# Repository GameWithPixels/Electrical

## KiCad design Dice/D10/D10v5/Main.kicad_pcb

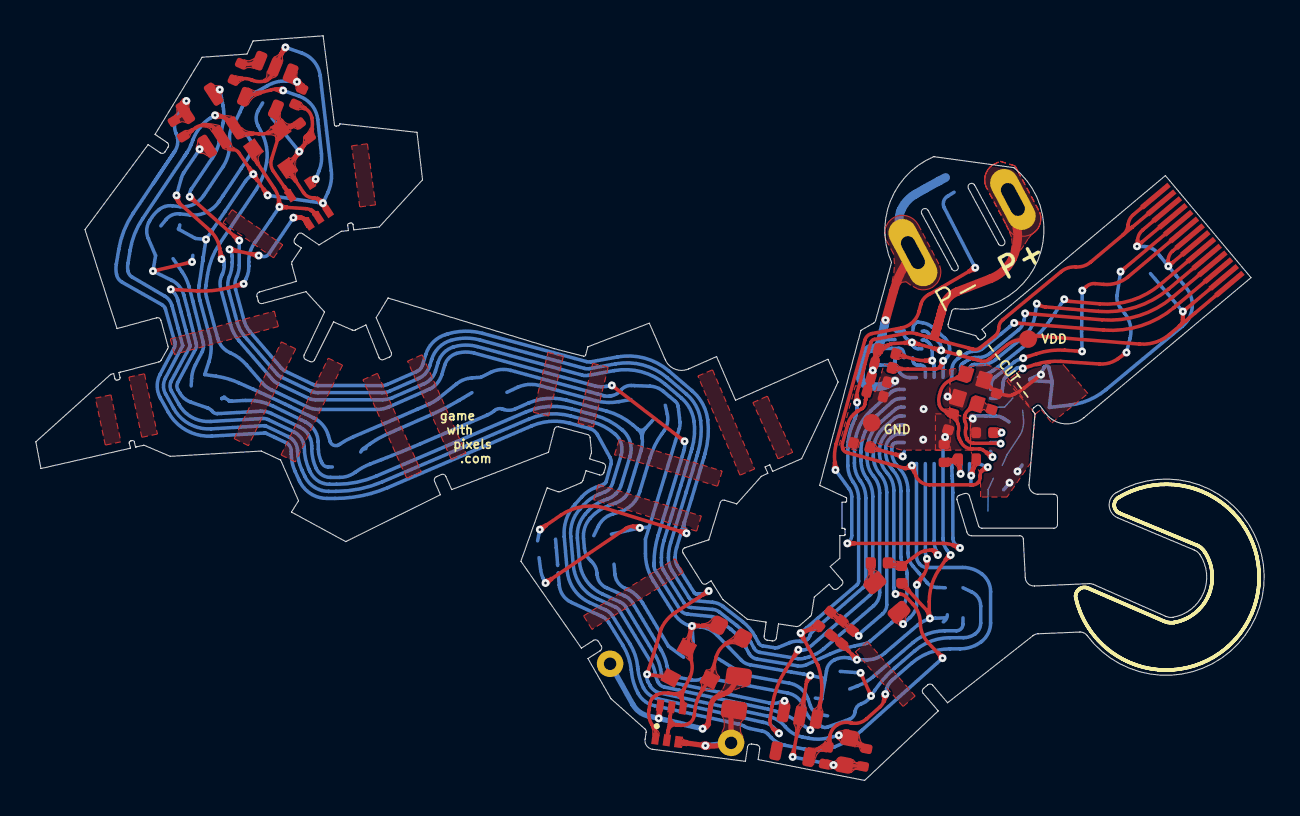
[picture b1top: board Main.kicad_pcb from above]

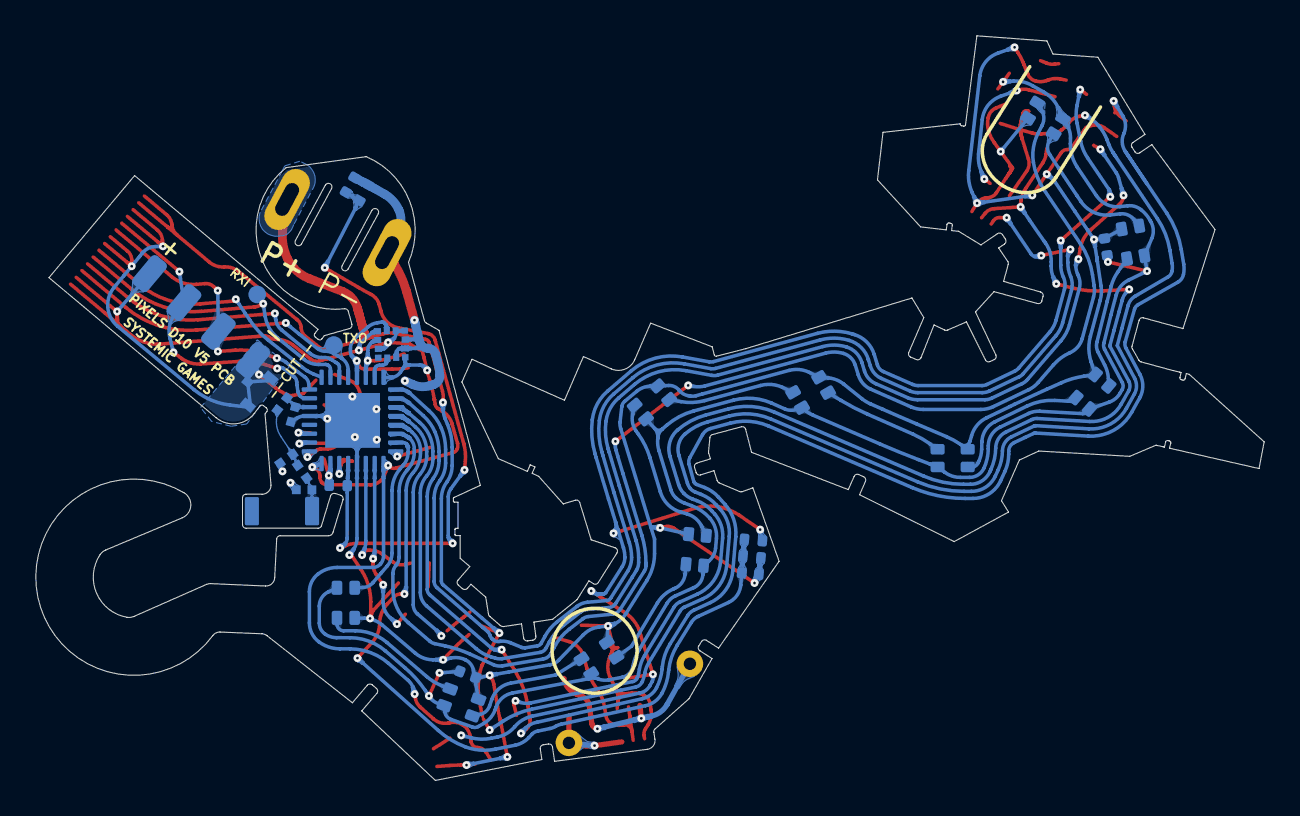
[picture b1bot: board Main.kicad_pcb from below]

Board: 2 copper layers, 69.4 x 42.1 mm, 69 parts (33 on the bottom side), 49 nets.

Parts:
AE1: Antenna_Chip; CHIP_ANT
C1, C4, C18: 4.7uF 10V 20%; C_0402_1005Metric
C2, C5: 8pF 10V 10%; C_0402_1005Metric
C3, C10, C23, C24: 0.1uF 10V 20%; C_0402_1005Metric
C6: DNP; C_0402_1005Metric
C7: 100pF NP0 10V 5%; C_0402_1005Metric
C8: 0.8pF 10V 5% C0G; 0402_RF
C9, C16: 10uF 10V 20%; C_0402_1005Metric
C11, C12: DNP; 0402_RF
C13: 4.7uF 25V 20%; C_0603_1608Metric
C15: 22uF 10V 20%; C_0603_1608Metric
C19: 12nF 50V 5% NP0; C_0805_2012Metric
C21, C22: 10nF 25V 10%; C_0402_1005Metric
D1: BAV99S; SOT-363_SC-70-6
D2, D3, D4, D5, D6, D7, D8, D9, D10, D11: TX1812Z_2020
J1: Conn_01x14; FPC_14
J2: Conn_01x04; FPC-POGO-4
J3: Conn_01x02; Hongjie 10100 Connector
J4: DNP; MFH3.RECE.20369.001E.01
L1: 10uH 100mA 20%; L_0805_2012Metric
L2: 15nH 100mA 5%; L_0402_1005Metric
L3: 0 Ohm; 0402_RF
L5: 3.9nH 5%; 0402_RF
P5: COILA; TestPoint_THTPad_D1.5mm_Drill0.7mm
P6: COILB; TestPoint_THTPad_D1.5mm_Drill0.7mm
R1, R2, R7: 4.02M 1%; R_0402_1005Metric
R3: 10k 5%; R_0402_1005Metric
R4, R5, R10: 100k 1%; R_0402_1005Metric
R6: 22k 1%; R_0402_1005Metric
R8: 10M 1%; R_0402_1005Metric
R9: 270k 1%; R_0402_1005Metric
R12, R16: 2.7k 5%; R_0402_1005Metric
TH1: NTC 100k @ 25C; R_0402_1005Metric
U1: N52810_QFN32; QFN-32-1EP_5x5mm_P0.5mm_EP3.1x3.1mm
U2: KXTJ3-1057; LGA-12_2x2mm_P0.5mm
U3: PJ75AL50SA; SOT-23
U4: ME6215; SOT-23-5
U5: MCP73832T-2ACI/OT; SOT-23-5
U6: MT9700; SOT-23-5
U7: SN74LVC1G08; SOT-353_SC-70-5
U8: TMR1366; SOT-23
W1: RXI; TEST_PIN
W2: TXO; TEST_PIN
W19: GND; TEST_PIN
W25: VDD; TEST_PIN
Y1: 32MHz 40ppm; Crystal_SMD_2016-4Pin_2.0x1.6mm

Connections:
+5V: C15.1, R1.1, R4.1, U3.2 (VOUT), U5.4 (VDD)
+BATT: C16.1, J1.1, J1.2, J3.1, R7.1, U4.1 (VIN), U5.3 (VBAT), U6.5 (VIN), U7.5 (VCC), U8.1 (VCC)
/5V_SENSE: C21.1, R1.2, R2.2, U1.4 (P0.04/AIN2)
/ACC_INT: U1.10 (P0.12), U2.5 (INT)
/ANTENNA: AE1.1 (FEED), C11.1, L3.2
/ANT_50: C12.1, J4.4 (RF), L3.1, L5.2
/ANT_NRF: C8.1, L5.1, U1.19 (ANT)
/BATT_NTC: C6.1, R5.2, TH1.1, U1.28 (P0.30/AIN6)
/LED_DATA: D2.1 (DIN), U1.2 (P0.00/XL1)
/LED_EN: U1.8 (P0.10), U7.1
/LED_RETURN: D11.3 (DOUT), U1.3 (P0.01/XL2)
/NTC_ID_VDD: R5.1, R10.2, U1.26 (P0.25)
/PROG: R6.1, U1.7 (P0.09), U5.5 (PROG)
/Power Supply/LED_EN_OUT: U6.4 (EN), U7.4
/Power Supply/MAG1_: U4.3 (CE), U7.2, U8.2 (OUT)
/SCL: R12.2, U1.12 (P0.15), U2.12 (SCL)
/SDA: R16.2, U1.11 (P0.14), U2.2 (SDA)
/STATS: U1.6 (P0.06), U5.1 (STAT)
/VBAT_SENSE: C22.1, R7.2, R8.1, U1.5 (P0.05/AIN3)
GND: C1.2, C2.1, C3.2, C4.2, C5.1, C6.2, C7.2, C8.2, C9.2, C10.2, C11.2, C12.2, C13.2, C15.2, C16.2, C18.2, C21.2, C22.2, C23.2, C24.2, D1.1 (A1), D1.4 (A3), D2.4 (GND), D3.4 (GND), D4.4 (GND), D5.4 (GND), D6.4 (GND), D7.4 (GND), D8.4 (GND), D9.4 (GND), D10.4 (GND), D11.4 (GND), J1.3, J1.4, J1.7, J1.8, J2.4, J3.2, J4.1, J4.2, J4.3, R2.1, R3.2, R4.2, R6.2, R8.2, R9.1, TH1.2, U1.20 (VSS), U1.29 (VSS), U1.33 (VSS), U2.6 (GND), U2.8 (GND), U2.9 (GND), U3.1 (VSS), U4.2 (VSS), U5.2 (VSS), U6.2 (GND), U7.3 (GND), U8.3 (GND), W19.1, Y1.2, Y1.4
unnamed: C1.1, L2.2, U1.30 (DEC4)
unnamed: C2.2, U1.24 (XC2), Y1.1
unnamed: C3.1, U1.1 (DEC1)
unnamed: C5.2, U1.23 (XC1), Y1.3
unnamed: C7.1, U1.22 (DEC3)
unnamed: C19.1, D1.3 (K1A2), P5.1
unnamed: C19.2, D1.6 (K3A4), P6.1
unnamed: D2.3 (DOUT), D3.1 (DIN)
unnamed: D3.3 (DOUT), D4.1 (DIN)
unnamed: D4.3 (DOUT), D5.1 (DIN)
unnamed: D5.3 (DOUT), D6.1 (DIN)
unnamed: D6.3 (DOUT), D7.1 (DIN)
unnamed: D7.3 (DOUT), D8.1 (DIN)
unnamed: D8.3 (DOUT), D9.1 (DIN)
unnamed: D9.3 (DOUT), D10.1 (DIN)
unnamed: D10.3 (DOUT), D11.1 (DIN)
unnamed: L1.1, U1.31 (DCC)
unnamed: L1.2, L2.1
unnamed: R3.1, U6.3 (SET)
unnamed: R9.2, R10.1, U1.27 (P0.28/AIN4)
RESET: J1.9, U1.16 (P0.16)
RXI: J1.10, U1.15 (P0.20/TCLK), W1.1
SWDCLK: J1.6, J2.3, U1.17 (SWDCLK)
SWDIO: J1.5, J2.2, U1.18 (SWDIO)
SWO: J1.11, U1.14 (P0.18/TDATA0)
TXO: J1.12, U1.13 (P0.16/TDATA1), W2.1
VDC: C9.1, C23.1, C24.1, D2.2 (VCC), D3.2 (VCC), D4.2 (VCC), D5.2 (VCC), D6.2 (VCC), D7.2 (VCC), D8.2 (VCC), D9.2 (VCC), D10.2 (VCC), D11.2 (VCC), U6.1 (VOUT)
VDD: C4.1, C10.1, C18.1, J1.13, J1.14, J2.1, R12.1, R16.1, U1.9 (VDD), U1.25 (VDD), U1.32 (VDD), U2.1 (ADDR), U2.3 (IO_VDD), U2.7 (VDD), U2.10 (VDD), U2.11 (IO_VDD), U4.5 (VOUT), W25.1
VEE: C13.1, D1.2 (K2), D1.5 (K4), U3.3 (VIN)
